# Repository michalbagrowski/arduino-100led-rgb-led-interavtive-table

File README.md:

# arduino-100led-rgb-led-interavtive-table
My playground for creating interactive table.

Inspiration for this is: http://www.it-gecko.de/100pixel-rgb-led-tisch-interaktiv-touch.html

Will try to add as much information as i can from point of view on noob in electronics :D

##CHANGELOG

# 26.03.2015

 * Trying to create PCB and schema in Eagle (http://www.cadsoftusa.com/download-eagle/freeware/) but it is to compilcated for beginer
 * I was told to try Fritzing (http://fritzing.org/home/) it's designed for Arduino and for for me now
   * Created first schema for "pixel" wish to solder 9 of them, to create 3x3 pixel table, only with RED LED there
   * Schematic avaliable in schematic/pixel/v0.0.1/
 * awsome first printend PCB for pixel 
 * unfortunetaly do not have small enought drill to start solvering ;/

# Before 24.03.2015

 * plaing with Arduino
 * burn few LED's beacuse not using resistors
 * burn one of IR reciver, becouse not reading Datasheet

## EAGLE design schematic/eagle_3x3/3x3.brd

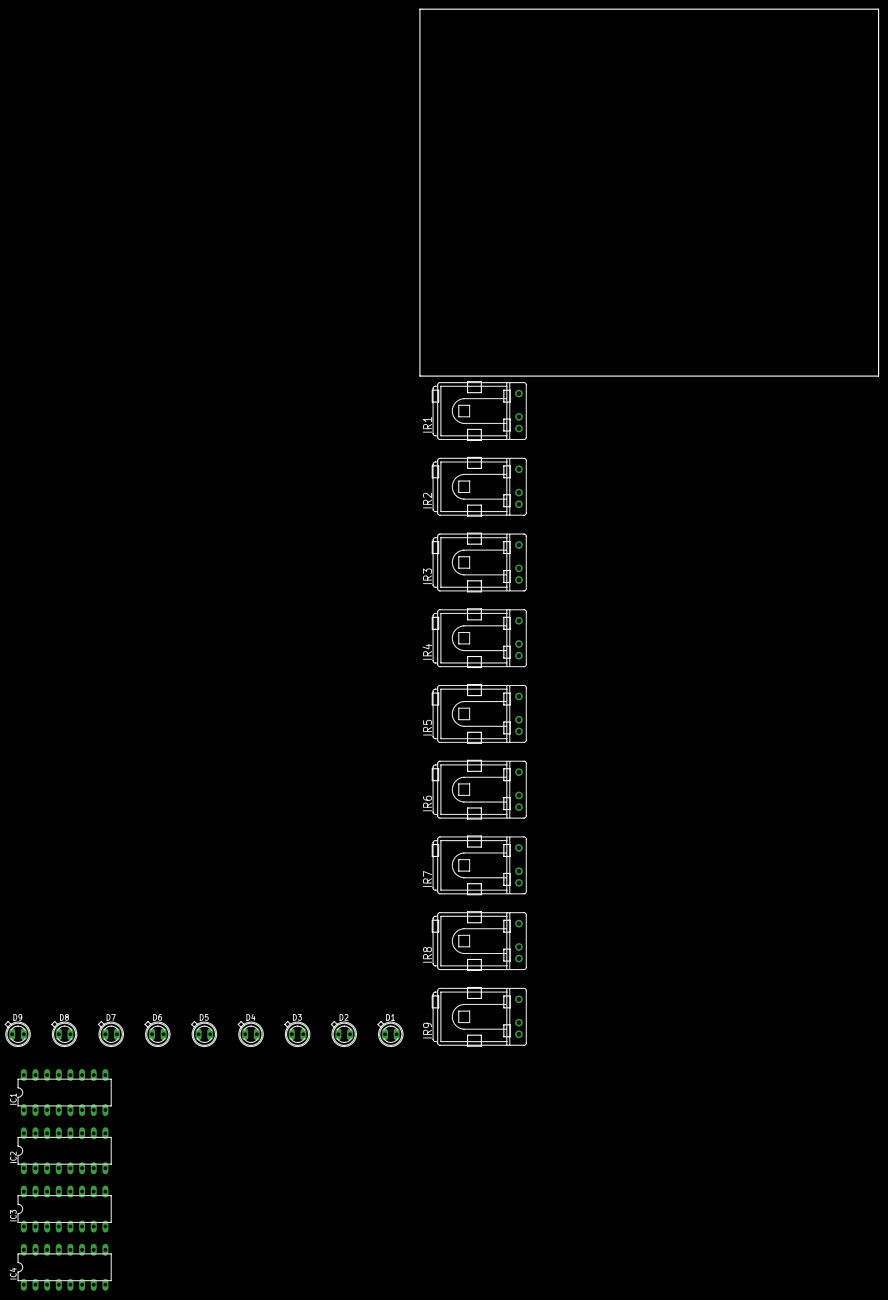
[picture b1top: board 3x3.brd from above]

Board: 2 copper layers, 22 parts (0 on the bottom side), 3 nets, no tracks yet.

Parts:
D1, D2, D3, D4, D5, D6, D7, D8, D9: SFH482
IC1, IC2, IC3, IC4: 74HC595N; DIL16
IR1, IR2, IR3, IR4, IR5, IR6, IR7, IR8, IR9: TSOP1737TB1; TSOP17_TB1

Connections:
GND: D1.K, D2.K, D3.K, D4.K, D5.K, D6.K, D7.K, D8.K, D9.K, IC1.8, IC1.13, IC2.8, IC2.13, IC3.8, IC3.13, IC4.8, IC4.13, IR1.GND, IR2.GND, IR3.GND, IR4.GND, IR5.GND, IR6.GND, IR7.GND, IR8.GND, IR9.GND
VCC: IC1.16, IC2.16, IC3.16, IC4.16, IR1.VO, IR2.VO, IR3.VO, IR4.VO, IR5.VO, IR6.VO, IR7.VO, IR8.VO, IR9.VO
VS: IR1.VS, IR2.VS, IR3.VS, IR4.VS, IR5.VS, IR6.VS, IR7.VS, IR8.VS, IR9.VS

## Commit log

2015-03-25 working simple prototype with 2 IR LEDs and 2 recivers... sadly without schematics...
2015-03-26 pixel v0.0.1
2015-03-26 pixel picture!
2015-03-26 fix readme formating
2015-03-26 add readme
2015-03-29 fun with LCD1602.
    ignore some mac files
2015-04-09 playing with shift out
2015-04-20 play with Eagle
